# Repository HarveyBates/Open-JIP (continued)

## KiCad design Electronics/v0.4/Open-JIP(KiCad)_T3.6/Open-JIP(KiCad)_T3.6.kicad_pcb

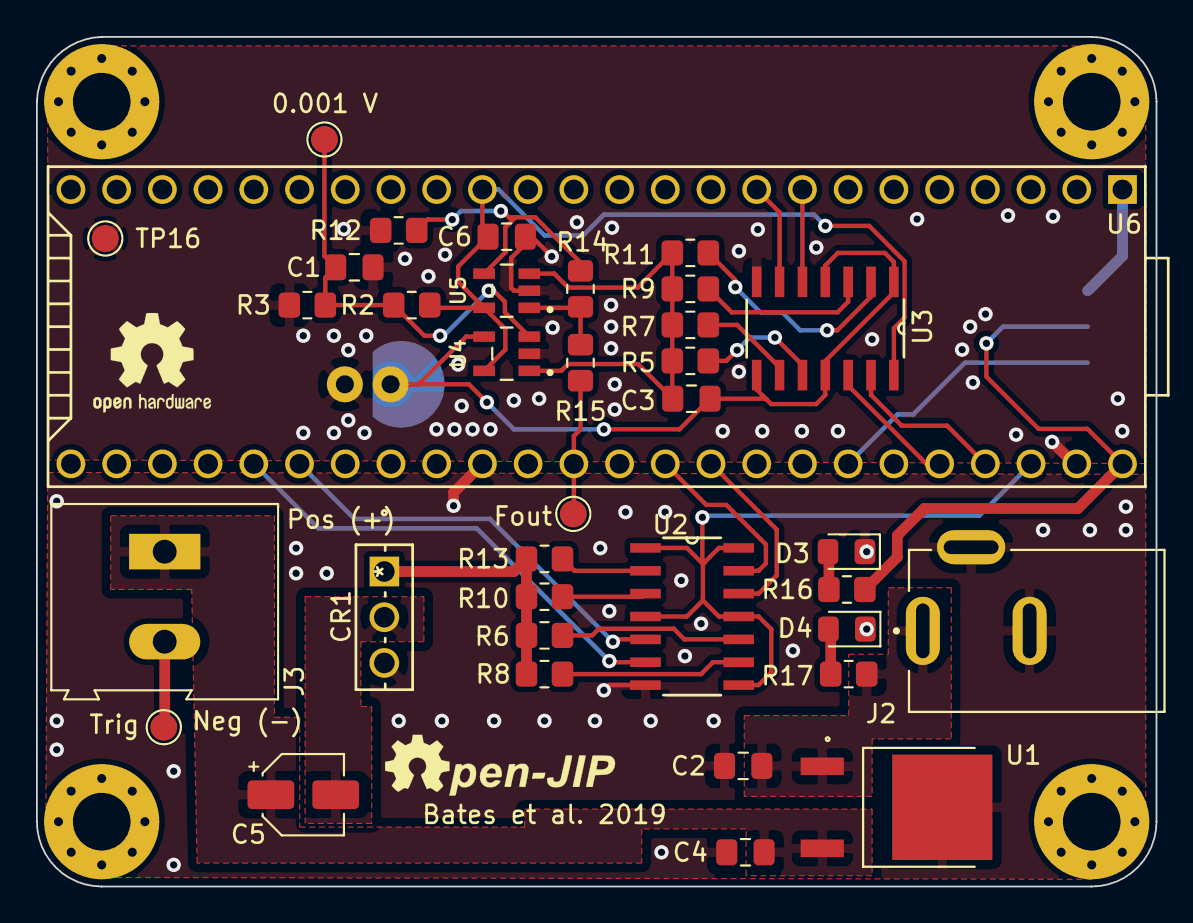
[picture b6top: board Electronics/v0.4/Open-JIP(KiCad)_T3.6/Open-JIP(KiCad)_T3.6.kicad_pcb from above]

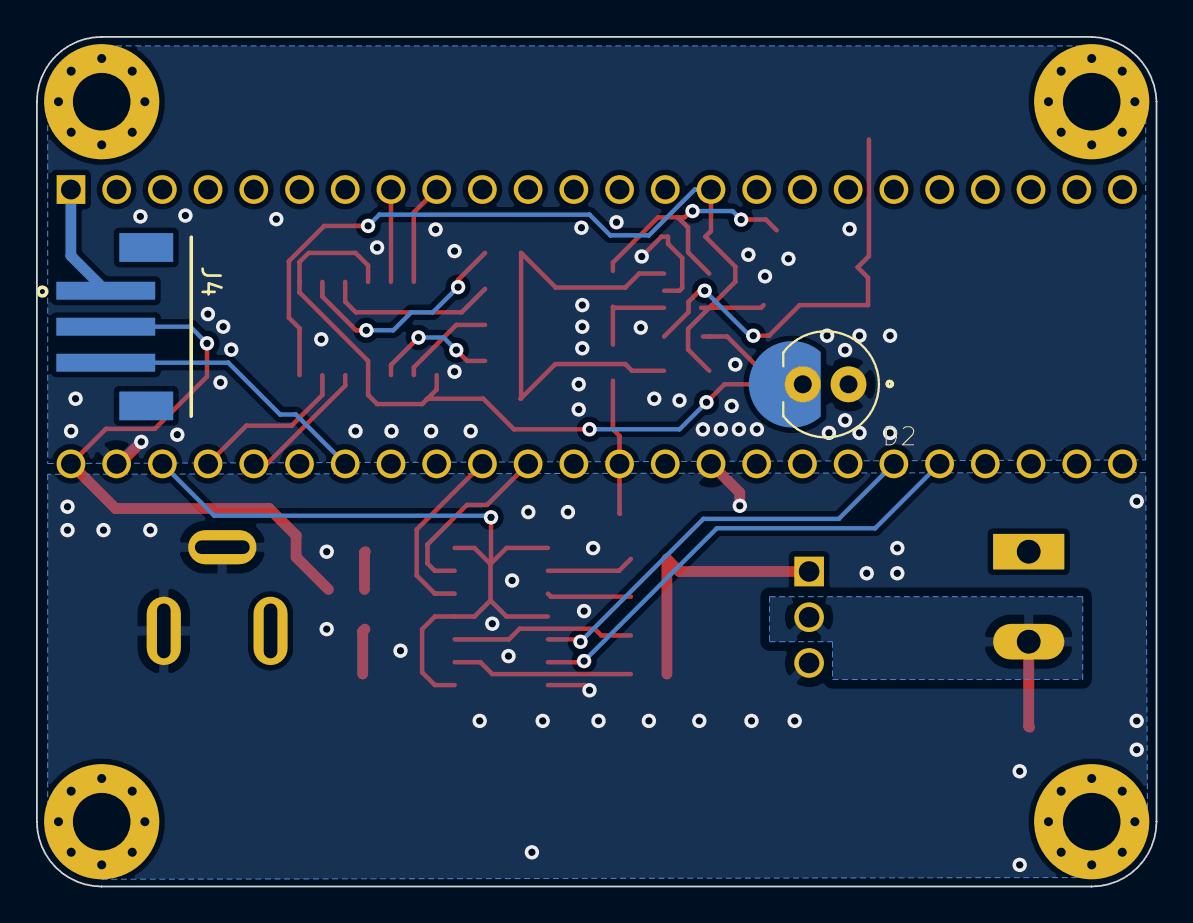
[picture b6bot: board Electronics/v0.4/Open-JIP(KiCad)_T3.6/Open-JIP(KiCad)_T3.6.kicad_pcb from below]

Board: 2 copper layers, 62.2 x 47.2 mm, 38 parts (2 on the bottom side), 33 nets.

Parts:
0.001 V: 0.001; TestPoint_Pad_D1.5mm
C1, C4, C6: 100nF; C_0805_2012Metric_Pad1.18x1.45mm_HandSolder
C2: 330nF; C_0805_2012Metric_Pad1.18x1.45mm_HandSolder
C3: 1pF; C_0805_2012Metric_Pad1.18x1.45mm_HandSolder
C5: 0.5uF; CP_Elec_4x5.4
CR1: BD681
D2: SFH_213_FA
D3, D4: LED; LED_0805_2012Metric_Pad1.15x1.40mm_HandSolder
Fout: OA-Out; TestPoint_Pad_D1.5mm
J2: EJ503A; DCJack_MPD_EJ503A
J3: Screw_Terminal_01x02; TerminalBlock_Altech_AK300-2_P5.00mm
J4: B3B-PH-SM4-TB(LF)(SN); JST_B3B-PH-SM4-TB(LF)(SN)
R2, R7: 20K; R_0805_2012Metric_Pad1.20x1.40mm_HandSolder
R3: 5; R_0805_2012Metric_Pad1.20x1.40mm_HandSolder
R5, R6: 10K; R_0805_2012Metric_Pad1.20x1.40mm_HandSolder
R8: 8.2K; R_0805_2012Metric_Pad1.20x1.40mm_HandSolder
R9, R14: 50K; R_0805_2012Metric_Pad1.20x1.40mm_HandSolder
R10: 6.8K; R_0805_2012Metric_Pad1.20x1.40mm_HandSolder
R11: 100K; R_0805_2012Metric_Pad1.20x1.40mm_HandSolder
R12: 300; R_0805_2012Metric_Pad1.20x1.40mm_HandSolder
R13: 5.1K; R_0805_2012Metric_Pad1.20x1.40mm_HandSolder
R15: 47; R_0805_2012Metric_Pad1.20x1.40mm_HandSolder
R16: 1K; R_0805_2012Metric_Pad1.20x1.40mm_HandSolder
R17: 15K; R_0805_2012Metric_Pad1.20x1.40mm_HandSolder
TP16: AGND; TestPoint_Pad_D1.5mm
Trig: TrigOut; TestPoint_Pad_D1.5mm
U1: L7806CD2T-TR; VREG_L7805CDT-TR
U2, U3: 74HC4066D,653; SOIC127P600X175-14N
U4, U5: OPA320AIDBVT; SOT95P280X145-5N
U6: Teensy3.6; Teensy35_36

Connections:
+3V3: C6.2, R2.2, U2.1, U2.4, U2.8, U2.11, U2.14, U3.14, U4.5, U5.5, U6.15, U6.51
+5V: J4.2, R16.1, U6.53
+12V: C2.2, J2.1, R17.1, U1.1
/-IN: C3.2, D2.2, U3.1, U3.4, U3.8, U3.11, U4.4
/Out: C3.1, R5.1, R7.1, R9.1, R11.1, U4.1, U5.3
/TrigOut: CR1.1, R6.1, R8.1, R10.1, R13.1
ActinicGain1: U2.13, U6.43
ActinicGain2: U2.5, U6.35
ActinicGain3: U2.6, U6.34
ActinicGain4: U2.12, U6.44
FluoroGain1: U3.13, U6.50
FluoroGain2: U3.5, U6.8
FluoroGain3: U3.6, U6.9
FluoroGain4: U3.12, U6.49
FluoroRead: Fout.1, R15.1, U6.41
GND: C2.1, C4.1, CR1.3, D3.1, D4.1, J2.2, J2.3, J4.1, U1.3, U2.7, U6.1, U6.39
GNDA: C1.1, C6.1, D2.1, R3.1, R12.1, TP16.1, U3.7, U4.2, U5.2, U6.52
unnamed: 0.001 V.1, C1.2, R2.1, R3.2, U4.3
unnamed: C4.2, C5.1, J3.1, U1.2
unnamed: C5.2, CR1.2, J3.2, Trig.1
unnamed: D3.2, R16.2
unnamed: D4.2, R17.2
unnamed: R5.2, U3.10
unnamed: R6.2, U2.10
unnamed: R7.2, U3.9
unnamed: R8.2, U2.9
unnamed: R9.2, U3.3
unnamed: R10.2, U2.3
unnamed: R11.2, U3.2
unnamed: R12.2, R14.2, U5.4
unnamed: R13.2, U2.2
unnamed: R14.1, R15.2, U5.1
ODEmitter: J4.3, U6.47

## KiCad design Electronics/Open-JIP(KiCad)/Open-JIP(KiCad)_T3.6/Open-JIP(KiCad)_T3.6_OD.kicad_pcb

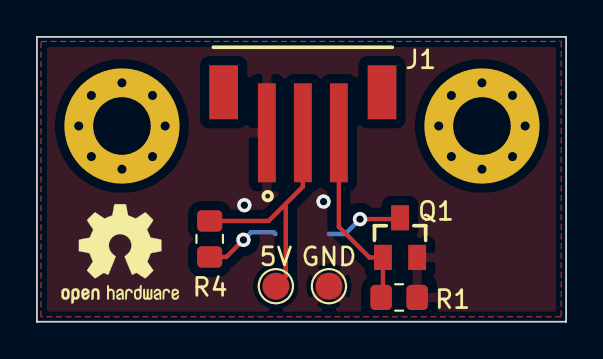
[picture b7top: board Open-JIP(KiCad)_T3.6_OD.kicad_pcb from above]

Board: 2 copper layers, 29.4 x 15.8 mm, 7 parts (1 on the bottom side), 5 nets.

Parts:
5V: 5VA; TestPoint_Pad_D1.5mm
D1: LED; LED_1206_3216Metric_Pad1.42x1.75mm_HandSolder
GND: GND1; TestPoint_Pad_D1.5mm
J1: B3B-PH-SM4-TB(LF)(SN); JST_B3B-PH-SM4-TB(LF)(SN)
Q1: FDN337N; SSOT-3
R1: 10K; R_0805_2012Metric_Pad1.20x1.40mm_HandSolder
R4: 220; R_0805_2012Metric_Pad1.20x1.40mm_HandSolder

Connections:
+5VA: 5V.1, J1.2, R4.2
GND1: GND.1, J1.1, Q1.2, R1.1
unnamed: D1.1, Q1.3
unnamed: D1.2, R4.1
ODEmitter1: J1.3, Q1.1, R1.2

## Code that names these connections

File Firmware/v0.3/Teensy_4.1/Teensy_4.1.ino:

/* <Open-JIP Teensy 4.1 Script. Controls "Open-JIP" chlorophyll fluorometer v0.3>
     Copyright (C) <2020>  <Harvey Bates>

     This program is free software: you can redistribute it and/or modify
     it under the terms of the GNU General Public License as published by
     the Free Software Foundation, either version 3 of the License, or
     (at your option) any later version.
     
     This program is distributed in the hope that it will be useful,
     but WITHOUT ANY WARRANTY; without even the implied warranty of
     MERCHANTABILITY or FITNESS FOR A PARTICULAR PURPOSE.  See the
     GNU General Public License for more details.
     
     You should have received a copy of the GNU General Public License
     along with this program.  If not, see <https://www.gnu.org/licenses/>
     
     For more information contact: harvey.bates@student.uts.edu.au or see
     https://github.com/HarveyBates/Open-JIP 
*/ 

/* Fluorescence intensity gain set pins */
/* These pins are backwards compatible between 3.6 and 4.1 */
int fluoroGain1 = 23;
int fluoroGain2 = 6;
int fluoroGain3 = 7;
int fluoroGain4 = 22;

/* Actinic intensity set pins */
/*
 * TODO: need to set these to PWM pins
 * Closeby pins that are compatible between 4.1 and 3.6 are:
 * - 9, 10, 29, 36, 37
int actinicGain1 = TODO: change this to a PWM pin (16 current pin)
int actinicGain2 = TODO: change this to a PWM pin (A22 current pin)
int actinicGain3 = TODO: change this to a PWM pin (A21 current pin)
int actinicGain4 = TODO: change this to a PWM pin (17 current pin)
*/

/* Fluorescence analogread pin */
#define readPin 14

// Setup arrays that hold fluorescence data
int microRead [1000];
int milliRead[1000];

// Setup arrays that hold timestamps that correspond to fluorescence values
float microTime[1000]; 
float milliTime[1000];
String command;

int microLength = 1000, milliLength = 1000; // Change these to match the size of the above arrays

// Setup arrays to hold all datapoints and corresponding timestamps
float fluorescenceValues[2000];
float timeStamps[2000];

int fm = 0; // Initalise the fm value so we can calcualte it later

int fo_pos = 4; // Location of Fo in the measured array

float refVoltage = 3.3; // Set the reference voltage (only applicable with Teensy 3.6)

void setup() {
  Serial.begin(115200); // Initalise serial communications at specific baud rate
  analogReadResolution(12); // Set the resolution of the microcontroller in bits
  pinMode(actinicPin, OUTPUT); // Set the actinic pin as an output
  digitalWrite(actinicPin, LOW); // Make sure the actinic LED is turned off
  pinMode(13, OUTPUT); // Sets the microcontrollers LED pin as an output
}

void measure_fluorescence() {
  
  digitalWrite(actinicPin, HIGH); // Turn on actinic LED

  long timer = micros(); // Start timer 

  // Read microsecond fluorescence values and corresponding timestamps
  for (unsigned int i = 0; i < sizeof(microRead) / sizeof(int); i++) 
  {
    microRead[i] = analogRead(readPin);
    microTime[i] = micros() - timer;
  }

  // Read millisecond fluorescence values and corresponding timestamps
  for (unsigned int i = 0; i < sizeof(milliRead) / sizeof(int); i++) 
  {
    milliRead[i] = analogRead(readPin);
    milliTime[i] = micros() - timer;
    delay(1);
  }
  
  digitalWrite(actinicPin, LOW); // Turn off actinic LED
  delay(10);

  // Convert micros() to milliseconds (ms) for microsecond values and convert bits to voltage
  for (unsigned int i = 0; i < sizeof(microRead) / sizeof(int); i++)
  {
   float milliReal = microTime[i]/1000; // Convert micros() to ms
   // Find fm value, we do this here while data are still ints
   if (microRead[i] > fm){
    fm = microRead[i];
   }
   fluorescenceValues[i] = (microRead[i] * refVoltage) / 4096; // Convert to volts and append to final array
   timeStamps[i] = milliReal; // Append time to final array
   Serial.print(milliReal, 3); 
   Serial.print("\t");
   Serial.println((microRead[i] * refVoltage) / 4096, 4);
   delay(1);
  }

  // Convert micros() to milliseconds for millsecond values and convert bits to voltage
  for (unsigned int i = 0; i < sizeof(milliRead) / sizeof(int); i++) 
  {
   float milliReal = milliTime[i]/1000; // Convert micros() to ms
   // Find fm value if not in microsecond range
   if (milliRead[i] > fm){
    fm = milliRead[i];
   }
   fluorescenceValues[i + microLength] = (milliRead[i] * refVoltage) / 4096; // Convert to V and append
   timeStamps[i + microLength] = milliReal; // Append to timestamps after microRead data
   Serial.print(milliReal, 3); 
   Serial.print("\t");
   Serial.println((milliRead[i] * refVoltage) / 4096, 4);
   delay(1);
  }
}

void calculate_parameters(){
  float fo = fluorescenceValues[fo_pos]; // Gets the minimum level fluorescence (Fo)
  float fj = 0.0f, fi = 0.0f;
  float  fj_time = 0.0f, fi_time = 0.0f, fm_time = 0.0f;
  bool fj_found = false, fi_found = false;

  // Next loop gets the Fj and Fi values at 2 and 30 ms respsctively 
  for(unsigned int i = 0; i < sizeof(timeStamps) / sizeof(int); i++){
    // Search for timestamp corresponding to 2 ms
    if(!fj_found && int(timeStamps[i]) == 2){
      fj = fluorescenceValues[i];
      fj_time = timeStamps[i];
      fj_found = true;
    }
    else if(!fi_found && int(timeStamps[i]) == 30){
      fi = fluorescenceValues[i];
      fi_time = timeStamps[i];
      fi_found = true;
    }
  }

  float fm_volts = (fm * refVoltage) / 4096.0;
  float fv = fm_volts - fo;
  float fvfm = fv / fm_volts;

  Serial.println();
  Serial.print("Fo: \t");
  Serial.print(fo, 4);
  Serial.print(" V @ ");
  Serial.print(timeStamps[fo_pos], 4);
  Serial.println(" ms");
  Serial.print("Fj: \t");
  Serial.print(fj, 4);
  Serial.println(" V @ " + String(fj_time) + " ms");
  Serial.print("Fi: \t");
  Serial.print(fi, 4);
  Serial.println(" V @ " + String(fi_time) + " ms");
  Serial.print("Fm: \t");
  Serial.print(fm_volts, 4);
  Serial.println(" V @ " + String(fm_time) + " ms");
  Serial.print("Fv: \t");
  Serial.print(fv, 4);
  Serial.println(" V");
  Serial.print("Quantum yield (Fv/Fm): \t");
  Serial.print(fvfm, 3);
  if(fvfm < 0.5){
    Serial.println(" Poor health");
  }
  else if(fvfm >= 0.5 && fvfm < 0.7){
    Serial.println(" Moderately healthy");
  }
  else if(fvfm >= 0.7){
    Serial.println(" Healthy");
  }
}

void calibrate_fo(){
  /* Calibrate the fo value of the fluorometer, can be used to ensure the concentration of algae
  is not too high
  */  
  float foread = 0.0f;
  for (int k = 0; k < 5; k++){
    digitalWrite(actinicPin, HIGH);
    delayMicroseconds(20);
    for (int i = 0; i <= 2; i++){
      foread = analogRead(readPin);
      Serial.println((foread/4096) * refVoltage);
    }
    digitalWrite(actinicPin, LOW);
    Serial.print("Final Fo = ");
    Serial.println((foread/4096) * refVoltage);
    delay(2000);
    }
}

void calibrate_rise(){
  // Calibrate the rise time of the flurometer (useful for debugging)
  for (int i = 0; i < 200; i++){
    digitalWrite(actinicPin, HIGH);
    delayMicroseconds(100);
    digitalWrite(actinicPin, LOW);
    delay(200);
  }
}

void measure_light(){
  // Measure light using external 4pi light meter
  digitalWrite(actinicPin, HIGH);
  delay(3000);
  digitalWrite(actinicPin, LOW);
  delay(20);
}

void loop(){
  if(Serial.available()){   
    command = Serial.readStringUntil('\n');
    if(command.equals("MeasureFluorescence") || command.equals("MF")){
      measure_fluorescence();
    }
    else if(command.equals("CP")){
      calculate_parameters();
    }
    else if(command.equals("CFo")){
      calibrate_fo();
    }
    else if(command.equals("ML")){
      measure_light();
    }
    else if(command.equals("Cr")){
      calibrate_rise();
    }
    else{
      delay(100);
    }
  }
  digitalWrite(13, HIGH);
  delay(1000);
  digitalWrite(13, LOW);
  delay(1000);
}

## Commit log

2018-12-12 Create LICENSE
2018-12-12 Create Open-JIP (Basic Operation)
2018-12-12 Rename Test_with_Arduino_as_Negitive_Input.ino to Open-JIP Basic Operation.ino
2019-05-17 PCB Open_JIP Gerber
2019-07-19 Add files via upload
    Bill of Materials for Open-JIP
2019-07-19 Update LICENSE
2019-07-19 Open-JIP Models
2020-09-09 major update
2020-09-09 generic update
2020-09-09 restructured main graphic scene
2020-09-10 preliminary tests with new plant measuring head
2020-09-11 needs work to improve signal integrity
2020-09-13 fixed inverted OJIP display on touch screen
2020-11-14 test
2020-11-14 updates for new version (v0.2)
2020-11-14 rm ds_store
2020-11-15 update readme and photos
2020-11-15 update BOM
2020-11-15 added pcb ordering info
2020-11-15 renaming things
2020-11-22 changed CB from pdf to gbr
2020-11-22 changed silkscreen
2020-11-22 added calculate parameters functionality
2020-11-22 added calculate parameters and improved comments
2020-11-23 updated documentation
2020-12-08 upgraded BOM and 3d-models
2020-12-11 started on v0.3
2020-12-14 fixed fvfm calculation
2020-12-14 adjustable fo position
2020-12-15 resiszed to fit quartz cuvette
2020-12-17 restructure and add teensy 4.1 support
2020-12-17 inital refactoring
2020-12-17 auto scan ports and upload data
2020-12-17 auto scan ports and csv upload function
2020-12-18 fixed indentation error
2020-12-18 update header
2020-12-18 added requirements.txt
2020-12-18 rename serial communications
2020-12-19 working on CSV to plot
2020-12-20 added plotting capability using plotly
2020-12-25 added adjustable gain for teensy 3.6
2020-12-25 started designing board for teensy 3.6
2020-12-26 finalised v0.3 for teensy 3.6
2020-12-26 started on v0.3 for teensy 3.2
2020-12-26 added v0.3 for teensy 3.1-2-LC
2020-12-26 finished v0.3 for teensy 3.2 and added gerber files
2020-12-27 rm fp-info-cache
2021-01-01 added readme for external control
2021-01-07 added some comments
2021-01-27 pre-working on v0.3 update
2021-01-27 added J-step measuring procedure
2021-01-27 added ability to measure consecutive O-J rises
2021-01-27 fixed loop variable name
2021-01-27 adjusted wave to output volts and ms
2021-01-29 fixed comment for wave rises
2021-02-02 adjustable sensitivty and intensity for v0.3
2021-02-07 adding UserManual for v0.3
2021-02-08 added UserManual and refactored readme
2021-02-10 fixed numbering direction
2021-02-16 update external cntrl
2021-02-19 update manual
2021-03-02 changed how the actinic LED is triggered
2021-03-04 increased sampling rate
2021-03-05 adding optical density to fluorometer
2021-03-07 od and fluorometer design
2021-03-11 refactored electronics desgin
2021-04-15 reconfigured array size setup
2021-04-24 fixed low reading due to analogReadResolution
2021-06-13 update actinic labels
2021-06-14 added get settings command
2021-07-10 updating structure and documentation
2021-07-14 updated v0.3 bom
2022-09-03 working on v1.0
2022-09-12 added precision current source for excitation LED
2022-09-19 finalised prototype components and started on PCB
2022-10-05 updated file structure of project
2022-10-05 further updates to file structure
2022-10-05 removed backup folders
2022-10-05 rename file structure for v0.3
2022-10-12 added some prelim firmware for v1.0, updated schematic and pcb to remove the second stage trans impedance amplifier on both detection excitation
2022-10-12 removed ibom file and added *.html to gitignore
2022-10-13 sent of two versions to be manufactured, one smd photodiode other with tht
2022-10-23 updates to version 1.0 with 18650 and new power supply
2023-09-05 update for next round of hardware testing
2023-09-07 updating PCB layout
2023-09-17 updated with two PCB's one detect, one excite, need to route the excite board and move the LED inline with cuvette
2023-09-19 working on cuvette mount and finished routing both pcbs
